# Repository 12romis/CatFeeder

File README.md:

# Cat Feeder — ESP32-C3 automatic feeder

Automatic dry food dispenser. An ESP32-C3 SuperMini drives a 28BYJ-48 stepper motor
through a ULN2003 module, turning a 3D-printed auger screw that dispenses food pellets.
Feeding is triggered by a time schedule or by a physical button press.
The device runs from a single 18650 cell and sleeps between events.

---

## Hardware

| Ref | Component | Notes |
|-----|-----------|-------|
| U2 | ESP32-C3 SuperMini | MCU + BLE 5.0 |
| U1 | TP4056 module | 18650 charging + protection |
| U3 | AP3602A boost module | 5 V rail for motor |
| M1 | ULN2003 driver module | stepper driver |
| SM1 | 28BYJ-48 stepper | auger drive |
| BT1 | 18650 Li-Ion cell | main power source |
| SW1 | Momentary push button | manual feed / wake |
| D1 | LED | status indicator |
| R1 | 220 Ω | LED current limit |
| C1 | 100 nF | power decoupling |
| C2 | 1000 µF | motor current buffer |

### Wiring

See schematic in [`schema/KiCad/cat_feeder.pdf`](schema/KiCad/cat_feeder.pdf)
or open the KiCad project at [`schema/KiCad/CatFeeder.kicad_sch`](schema/KiCad/CatFeeder.kicad_sch).

**Pin map (ESP32-C3 SuperMini):**

| GPIO | Connects to | Direction |
|------|-------------|-----------|
| 2 | ULN2003 IN1 | OUT |
| 3 | ULN2003 IN2 | OUT |
| 4 | ULN2003 IN3 | OUT |
| 5 | ULN2003 IN4 | OUT |
| 8 | LED via 220 Ω to GND | OUT |
| 9 | Button to GND (INPUT\_PULLUP) | IN / wake |
| 10 | AP3602A boost EN | OUT |

Power path: `18650 → TP4056 → ESP32-C3 VIN` (always on)
and `18650 → TP4056 → AP3602A VIN → 5 V → ULN2003 + motor` (switched via GPIO 10).

---

## Software setup

### Requirements

- [VS Code](https://code.visualstudio.com/) with the
  [PlatformIO IDE](https://platformio.org/install/ide?install=vscode) extension
- USB cable (the C3 SuperMini uses native USB — port appears as `/dev/ttyACM0` on Linux)

### Build and flash

1. Open the **`CatFeeder/`** folder in VS Code (it is the PlatformIO project root).
2. Select the environment:
   - `c3` — ESP32-C3 SuperMini (production target)
   - `s3` — ESP32-S3 DevKitC-1 (breadboard test; same GPIO numbers)
3. Click **Upload** in the PlatformIO toolbar, or run:

```bash
pio run -e c3 --target upload
```

4. Open the Serial Monitor at **115200 baud**:

```bash
pio device monitor -e c3
```

> **Flash mode on C3 SuperMini:** if the board doesn't enter download mode automatically,
> hold **BOOT (GPIO 9)** while pressing **RESET**, then release RESET.

---

## First-run configuration via Serial console

All configuration is done by typing commands in the PlatformIO Serial Monitor
(line ending: `\n` or `\r\n`).

### 1. Configure Wi-Fi for automatic time sync (one-time setup)

The device has no RTC chip. On every cold boot (power-on after battery removed or
discharged) it connects to Wi-Fi, fetches UTC time from NTP, then immediately
disconnects. Wi-Fi is **never used after deep-sleep wakes** — only on cold boot.

```
WIFI_SSID MyNetwork
WIFI_PASS mypassword
```

Credentials are saved to flash and never need to be entered again.
If Wi-Fi is unavailable, the device falls back to manual time entry:

```
SET_TIME 1750420800
```

Get the current Unix epoch in your terminal:

```bash
date +%s
```

### 2. Set the feeding schedule

Times are in **UTC**. Up to 8 entries, space-separated.

```
SCHED 07:00 18:30
```

The schedule is saved to flash (NVS) and survives power-off.

Between scheduled feeds the device is in deep sleep. It wakes automatically at each
scheduled time, runs the motor, then sleeps until the next entry.

**Scheduled feed limits** (config.h):

| Limit | Default | Description |
|-------|---------|-------------|
| `MAX_PORTIONS_PER_DAY` | 4 | Max scheduled feeds per day; extras are skipped |
| `MIN_INTERVAL_SEC` | 1800 s | Min gap between scheduled feeds (30 min) |

These limits apply **only to the schedule**. Button press and `FEED` serial command
are always allowed regardless of how recently the motor ran.

### 3. Calibrate portion size

Portion size is defined in **stepper steps**, not time. Calibrate by weighing:

```
CAL 512       ← run motor 512 steps; weigh the dispensed food
CAL 768       ← try a different value
SAVE          ← commit the chosen step count to flash
```

Repeat `CAL` until the dispensed amount matches the desired portion weight.
`SAVE` must be sent explicitly — until then the new value is not persisted.

### 4. Verify

```
STATUS        ← show time, steps, portionsToday, schedule with next feed countdown
FEED          ← manual feed (no limits)
RESET_DAY     ← zero portionsToday and lastFeedEpoch (for testing)
```

---

## All Serial commands

| Command | Description |
|---------|-------------|
| `WIFI_SSID <ssid>` | Save Wi-Fi network name to flash |
| `WIFI_PASS <pass>` | Save Wi-Fi password to flash |
| `WIFI_SYNC` | Connect and sync time via NTP now |
| `SET_TIME <epoch>` | Set wall clock manually (Unix seconds UTC) |
| `SCHED HH:MM [HH:MM ...]` | Set feeding schedule (UTC, up to 8 entries) |
| `CAL <steps>` | Run motor N steps without counting as a feed |
| `SAVE` | Save the last CAL step count to flash |
| `FEED` | Dispense one portion (no limits) |
| `STATUS` | Print current device state incl. schedule and Wi-Fi SSID |
| `RESET_DAY` | Zero portionsToday and lastFeedEpoch |

---

## Button behaviour

| Press | Action |
|-------|--------|
| Short press | Dispense one portion |
| Double click (gap < 300 ms) | Dispense two portions |
| Long press ≥ 2 s | Enter deep sleep immediately without feeding |

---

## Power notes

- The device enters deep sleep between feeds. Wake sources: button or RTC timer.
- The 5 V motor rail (boost converter) is switched on only during a dose, then cut.
- Always-on current in deep sleep: ~50–100 µA (ESP32-C3 + LDO quiescent).
- Expected battery life on 3000 mAh 18650 with 4 feeds/day: **several months**.

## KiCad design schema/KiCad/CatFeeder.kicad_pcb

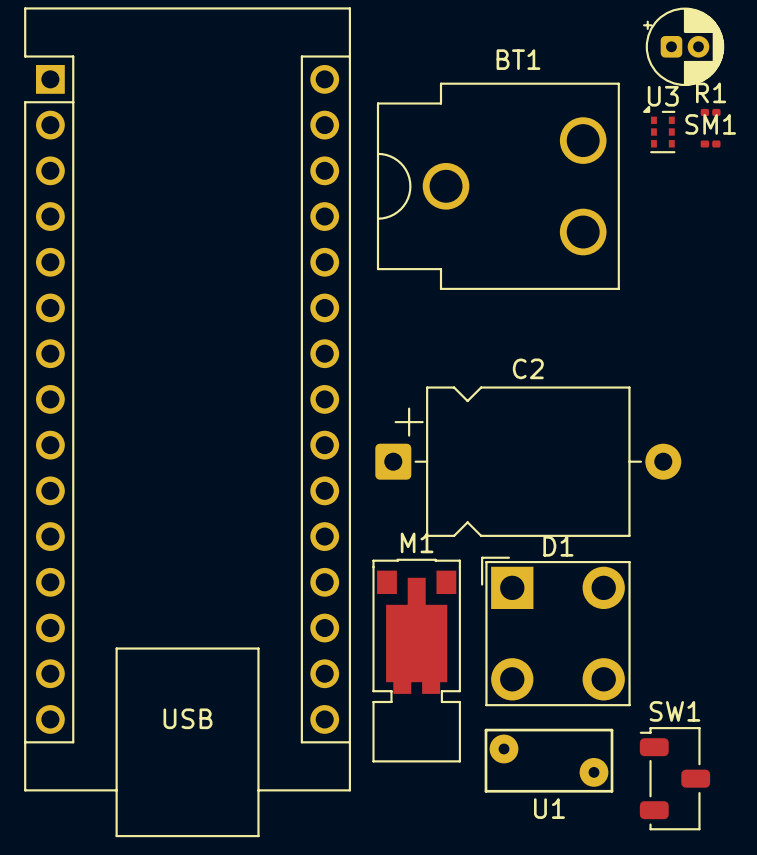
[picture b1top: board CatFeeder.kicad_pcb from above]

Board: 2 copper layers, 11 parts (0 on the bottom side), 9 nets, no tracks yet.

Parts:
BT1: 18650 3.7V; BatteryClip_Keystone_54_D16-19mm
C1: 100nF; CP_Radial_D4.0mm_P1.50mm
C2: 1000uF; CP_Axial_L11.0mm_D8.0mm_P15.00mm_Horizontal
D1: LED; LED_BL-FL7680RGB
M1: ULN2003 Driver Module; Vybronics_VZ30C1T8219732L
R1: 220; R_0201_0603Metric
SM1: 28BYJ-48; R_0201_0603Metric
SW1: Button (wake); Nidec_Copal_CAS-120A
U1: TP4056; RV_Disc_D7mm_W3.4mm_P5mm
U2: ESP32-C3 SuperMini; Arduino_Nano
U3: AP3602A Boost 5V; Anaren_0805_2012Metric-6

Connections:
unnamed: C1.1 (+), C2.2, D1.2 (K), SW1.1, U1.2 (OUT-), U2.3 (GND), U3.2 (GND)
unnamed: C1.2 (-), U1.1 (OUT+), U2.1 (5V), U3.1 (VIN)
unnamed: D1.1 (A), R1.1
unnamed: M1.1 (IN1), U2.4 (GPIO2_IN1)
unnamed: M1.2 (IN2), U2.5 (GPIO3_IN2)
unnamed: C2.1, U3.3 (VOUT(5V))
unnamed: R1.2, U2.10 (GPIO8_LED)
unnamed: SW1.2, U2.8 (GPIO9_BTN)
unnamed: U2.9 (GPIO10_EN), U3.4 (EN)

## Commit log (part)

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2026-06-20 added fzz to readme
2026-06-21 fixes after first run on s3 and breadboard
2026-06-21 added first time sync via wifi
2026-06-21 double feed by double click
